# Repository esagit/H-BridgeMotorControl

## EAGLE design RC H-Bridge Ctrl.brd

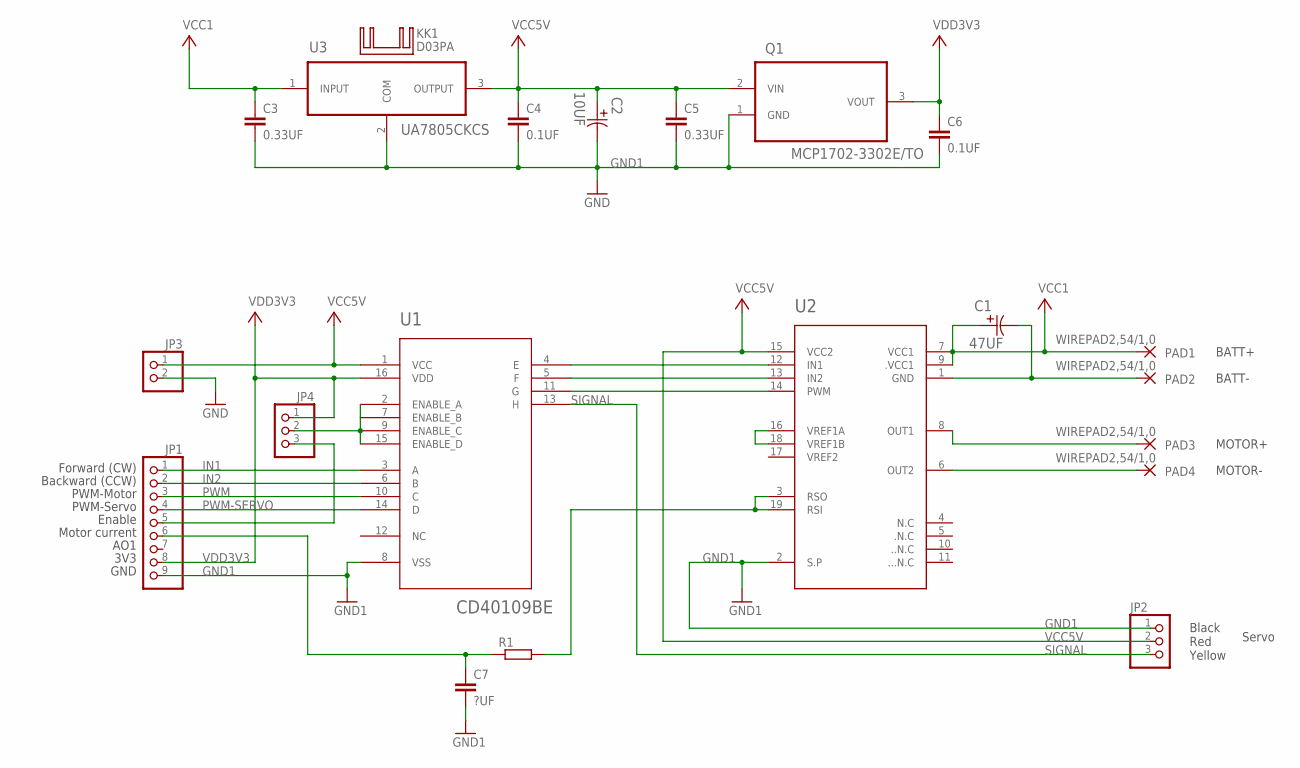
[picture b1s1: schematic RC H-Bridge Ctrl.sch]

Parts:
C1: 47UF; CAPPR200-500X1100
C2: 10UF; CAPPR200-500X1100
C3, C5: 0.33UF; C5B3
C4, C6: 0.1UF; C5B3
C7: ?UF; C5B3
JP1: PINHD-1X9; 1X09
JP2, JP4: PINHD-1X3; 1X03
JP3: PINHD-1X2; 1X02
KK1: D03PA
PAD1, PAD2, PAD3, PAD4: WIREPAD2,54/1,0; 2,54/1,0
Q1: MCP1702-3302E/TO; TO127P254X533-3
R1: R-EU_0204/7; 0204/7
U1: CD40109BE; DIL16
U2: STK681-360-E; SIP-19
U3: UA7805CKCS; TO254P457X1016X2222-3P

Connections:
AI0: C7.1, JP1.6, R1.1
AO0: R1.2, U2.3 (RSO), U2.19 (RSI)
GND1: C2.2, C3.2, C4.2, C5.2, C6.2, C7.2, JP1.9, JP2.1, JP3.2, Q1.1 (GND), U1.8 (VSS), U2.2 (S.P), U3.2 (COM)
IN1: JP1.1, U1.3 (A)
IN2: JP1.2, U1.6 (B)
unnamed: PAD3.1, U2.8 (OUT1)
unnamed: PAD4.1, U2.6 (OUT2)
unnamed: JP4.2, U1.2 (ENABLE_A), U1.7 (ENABLE_B), U1.9 (ENABLE_C), U1.15 (ENABLE_D)
unnamed: JP1.5, JP4.3
unnamed: U1.4 (E), U2.12 (IN1)
unnamed: C1.2, PAD2.1, U2.1 (GND)
unnamed: U1.5 (F), U2.13 (IN2)
unnamed: U1.11 (G), U2.14 (PWM)
unnamed: U2.16 (VREF1A), U2.18 (VREF1B)
PWM: JP1.3, U1.10 (C)
PWM-SERVO: JP1.4, U1.14 (D)
SIGNAL: JP2.3, U1.13 (H)
VCC1: C1.1, C3.1, PAD1.1, U2.7 (VCC1), U2.9 (.VCC1), U3.1 (INPUT)
VCC5V: C2.1, C4.1, C5.1, JP2.2, JP3.1, Q1.2 (VIN), U1.1 (VCC), U2.15 (VCC2), U3.3 (OUTPUT)
VDD3V3: C6.1, JP1.8, JP4.1, Q1.3 (VOUT), U1.16 (VDD)

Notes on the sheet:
BATT+
MOTOR+
MOTOR-
BATT-
Black Red Yellow
Servo
Forward (CW) Backward (CCW) PWM-Motor PWM-Servo Enable Motor current AO1 3V3 GND

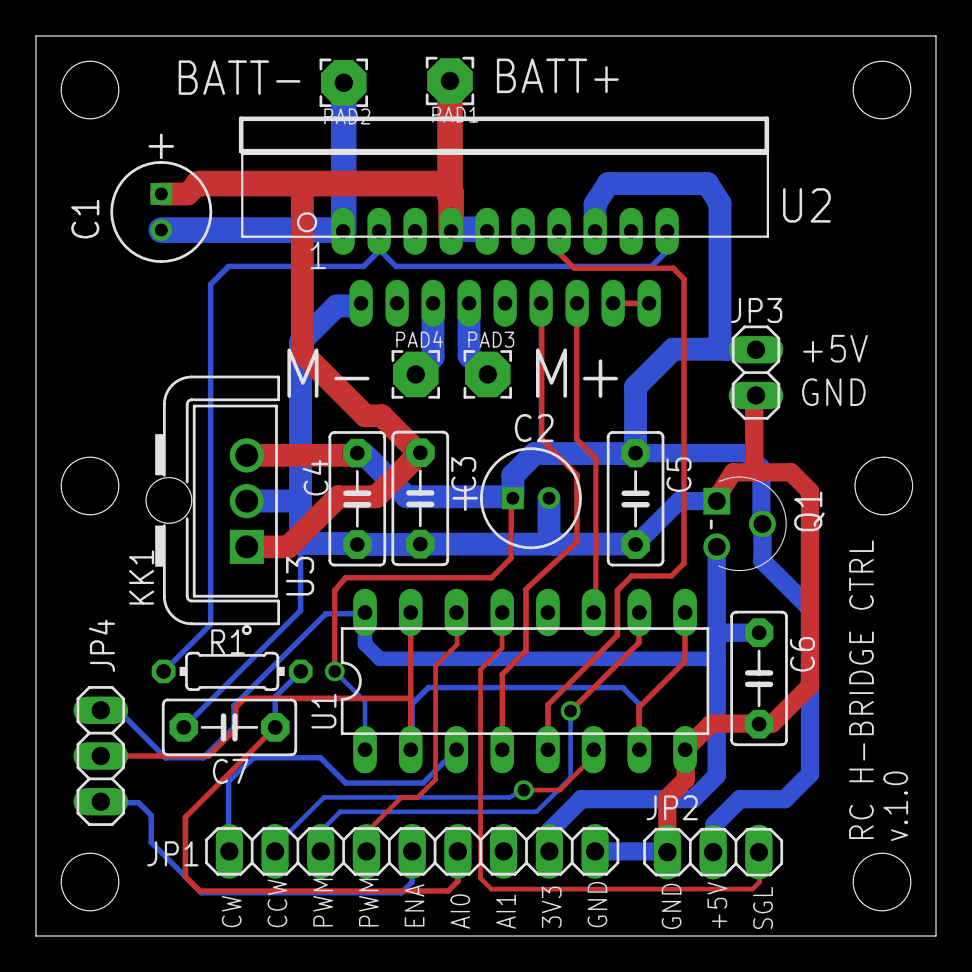
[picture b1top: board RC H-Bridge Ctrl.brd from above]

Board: 2 copper layers, 50.0 x 50.0 mm, 21 parts (0 on the bottom side), 20 nets.

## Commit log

2017-10-20 :boom::camel: Added .gitattributes & .gitignore files
2017-10-20 Initial commit
    Initial commit
